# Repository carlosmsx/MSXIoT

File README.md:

# MSX IoT

## Internet de las cosas para MSX
Si estás en este sitio probablemente ya sabes lo que es un MSX.
Pero, has oído hablar de Internet de las cosas (Internet of Things)?
Te presento MSX IoT.

Es un cartucho para MSX que permite IoT y algunos extras muy interesantes:

* Conectarse a redes WiFi
* Conectarse a dispositivos BT
* Conectarse a dispositivos seriales (TTL)
* Audio
* Disco en la nube
* Unidades de red

Una vez conectado a una red WiFi, las posibilidades son muchas. Por ejemplo, es posible comandar dispositivos a través de internet, o bien saber el estado de los mismos.

A nivel de hardware, MSX IoT consta de una ROM, un decodificador de direcciones y un módulo ESP32.

Cada vez que el Z80 accede para lectura o escritura a un puerto designado en el decodificador, se genera una señal WAIT hacia el Z80 y paralelamente se lanza una interrupción en el ESP32. Esto permite que en el microcontrolador se compruebe si la interrupción se debe a una operación de entrada o salida. Con esto el ESP32 puede leer bytes enviados por el Z80, o bien enviarlos a solicitud del mismo. Es decir, el microcontrolador trabaja en modo esclavo. De esta manera es posible establecer intercambio de datos controlados desde el Z80. 

## Otras posibles habilidades del cartucho

### Cloud disk
Para esto es necesario implementar una unidad de disco que permita acceder a un repositorio en la nube. Sería ideal si se pudiese conectar a por ejemplo google drive. 
Mapear una unidad de red a una carpeta compartida de windows o linux.
### Audio
El ESP32 tiene la posibilidad de generar audio a través de dos salidas que poseen un DAC. Sabiendo esto, el cartucho tiene previsto evolucionar sobre este punto de manera de conectar estas salidas a la entrada de audio de MSX. En teoría sería posible generar sonidos tan complejos como la programación del ESP32 lo permita.
### RS232 TTL
Se ha dejado disponible una UART en el cartucho de manera que el cartucho sirva como una interfaz serie. 
Sería necesario implementar las extensiones BASIC correspondientes
- CALL COMBREAK
- CALL COMDTR
- CALL COM GOSUB
- CALL COMHELP
- CALL COMINI
- CALL COMOFF
- CALL COMON
- CALL COMSTAT
- CALL COMSTOP
- CALL COMTERM

© Carlos Escobar 2019

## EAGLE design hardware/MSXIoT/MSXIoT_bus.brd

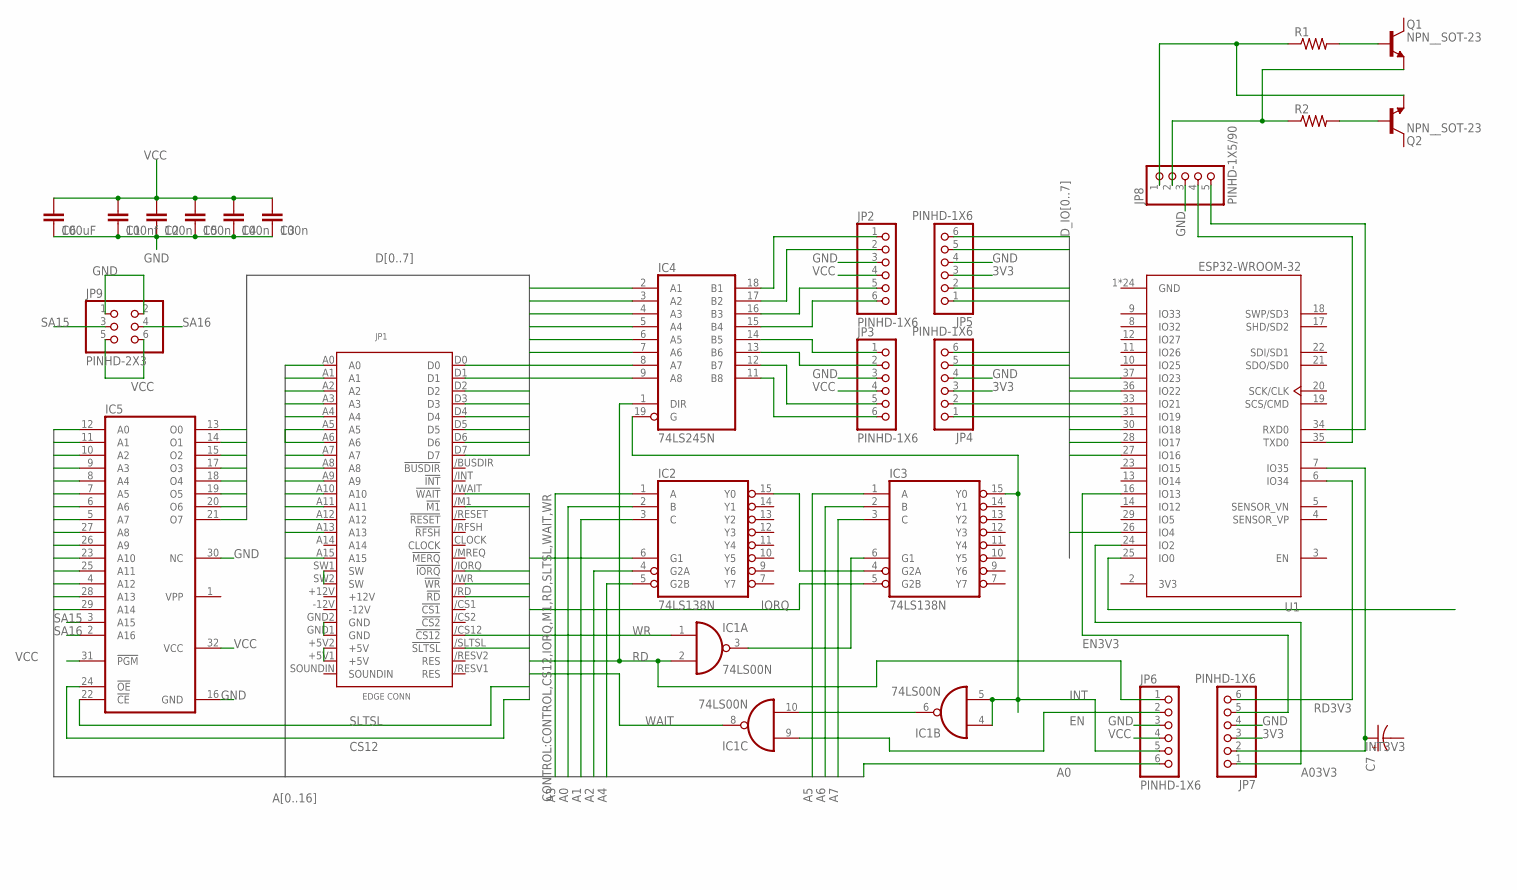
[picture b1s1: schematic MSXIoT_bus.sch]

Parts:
C1: 100nf; C2.5-2
C2, C3, C4, C5: 100n; C2.5-3
C6: 100uF; C2.5-6
C7: CPOL-US153CLV-0505; 153CLV-0505
IC1: 74LS00N; DIL14
IC2, IC3: 74LS138N; DIL16
IC4: 74LS245N; DIL20
IC5: 27C1001A; DIL32
JP1: MSXCART
JP2, JP3, JP4, JP5, JP6, JP7: PINHD-1X6; 1X06
JP8: PINHD-1X5/90; 1X05/90
JP9: PINHD-2X3; 2X03
Q1, Q2: NPN__SOT-23; SOT95P237X112-3N
R1, R2: R-US_0204/5; 0204/5
U1: ESP32-WROOM-32; MODULE_ESP32-WROOM-32

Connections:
3V3: JP4.3, JP5.3, JP7.3, U1.2 (3V3)
A0: IC2.2 (B), IC5.12 (A0), JP1.A0, JP6.6
A1: IC2.3 (C), IC5.11 (A1), JP1.A1
A2: IC2.4 (G2A), IC5.10 (A2), JP1.A2
A3: IC2.1 (A), IC5.9 (A3), JP1.A3
A03V3: JP7.1, U1.24 (IO2)
A4: IC2.5 (G2B), IC5.8 (A4), JP1.A4
A5: IC3.1 (A), IC5.7 (A5), JP1.A5
A6: IC3.2 (B), IC5.6 (A6), JP1.A6
A7: IC3.3 (C), IC5.5 (A7), JP1.A7
A8: IC5.27 (A8), JP1.A8
A9: IC5.26 (A9), JP1.A9
A10: IC5.23 (A10), JP1.A10
A11: IC5.25 (A11), JP1.A11
A12: IC5.4 (A12), JP1.A12
A13: IC5.28 (A13), JP1.A13
A14: IC5.29 (A14), JP1.A15
CS12: IC5.24 (!OE), JP1./CS12 (!CS12)
D0: IC4.2 (A1), IC5.13 (O0), JP1.D0
D1: IC4.3 (A2), IC5.14 (O1), JP1.D1
D2: IC4.4 (A3), IC5.15 (O2), JP1.D2
D3: IC4.5 (A4), IC5.17 (O3), JP1.D3
D4: IC4.6 (A5), IC5.18 (O4), JP1.D4
D5: IC4.7 (A6), IC5.19 (O5), JP1.D5
D6: IC4.8 (A7), IC5.20 (O6), JP1.D6
D7: IC4.9 (A8), IC5.21 (O7), JP1.D7
D_IO0: JP5.6, U1.37 (IO23)
D_IO1: JP5.5, U1.36 (IO22)
D_IO2: JP5.2, U1.33 (IO21)
D_IO3: JP5.1, U1.31 (IO19)
D_IO4: JP4.6, U1.30 (IO18)
D_IO5: JP4.5, U1.28 (IO17)
D_IO6: JP4.2, U1.27 (IO16)
D_IO7: JP4.1, U1.26 (IO4)
EN: IC1.9 (I0), JP6.2
EN3V3: JP7.5, U1.16 (IO13)
GND: C1.2, C2.2, C3.2, C4.2, C5.2, C6.2, IC1.7 (GND), IC2.8 (GND), IC3.8 (GND), IC4.10 (GND), IC5.16 (GND), IC5.30 (NC), JP1.GND1 (GND), JP1.GND2 (GND), JP2.3, JP3.3, JP4.4, JP5.4, JP6.3, JP7.4, JP8.3, JP9.1, JP9.2, U1.1 (GND), U1.15 (GND), U1.38 (GND), U1.39_1 (GND), U1.39_2 (GND), U1.39_3 (GND), U1.39_4 (GND), U1.39_5 (GND), U1.39_6 (GND), U1.39_7 (GND), U1.39_8 (GND), U1.39_9 (GND), U1.39_10 (GND), U1.39_11 (GND), U1.39_12 (GND), U1.39_13 (GND), U1.39_14 (GND), U1.39_15 (GND), U1.39_16 (GND), U1.39_17 (GND), U1.39_18 (GND), U1.39_19 (GND), U1.39_20 (GND), U1.39_21 (GND)
INT: IC1.4 (I0), IC1.5 (I1), IC3.15 (Y0), IC4.19 (G), JP6.5
INT3V3: C7.+, JP7.2, U1.7 (IO35)
IORQ: IC3.5 (G2B), JP1./IORQ (!IORQ)
M1: IC2.6 (G1), JP1./M1 (!M1)
unnamed: IC1.6 (O), IC1.10 (I1)
unnamed: IC4.18 (B1), JP2.1
unnamed: IC2.15 (Y0), IC3.4 (G2A)
unnamed: IC1.3 (O), IC3.6 (G1)
unnamed: IC4.17 (B2), JP2.2
unnamed: IC4.16 (B3), JP2.5
unnamed: IC4.15 (B4), JP2.6
unnamed: IC4.14 (B5), JP3.1
unnamed: IC4.13 (B6), JP3.2
unnamed: IC4.12 (B7), JP3.5
unnamed: IC4.11 (B8), JP3.6
unnamed: JP1.SW1 (SW), JP1.SW2 (SW)
unnamed: JP8.4, U1.35 (TXD0)
unnamed: JP8.5, U1.34 (RXD0)
unnamed: JP8.1, Q2.1 (E), R1.1
unnamed: Q1.2 (B), R1.2
unnamed: Q2.2 (B), R2.2
unnamed: JP8.2, Q1.1 (E), R2.1
RD: IC1.2 (I1), IC4.1 (DIR), JP1./RD (!RD), JP6.1
RD3V3: JP7.6, U1.6 (IO34)
SA15: IC5.3 (A15), JP9.3
SA16: IC5.2 (A16), JP9.4
SLTSL: IC5.22 (!CE), JP1./SLTSL (!SLTSL)
VCC: C1.1, C2.1, C3.1, C4.1, C5.1, C6.1, IC1.14 (VCC), IC2.16 (VCC), IC3.16 (VCC), IC4.20 (VCC), IC5.31 (!PGM), IC5.32 (VCC), JP1.+5V1 (+5V), JP1.+5V2 (+5V), JP2.4, JP3.4, JP6.4, JP9.5, JP9.6
WAIT: IC1.8 (O), JP1./WAIT (!WAIT)
WR: IC1.1 (I0), JP1./WR (!WR)

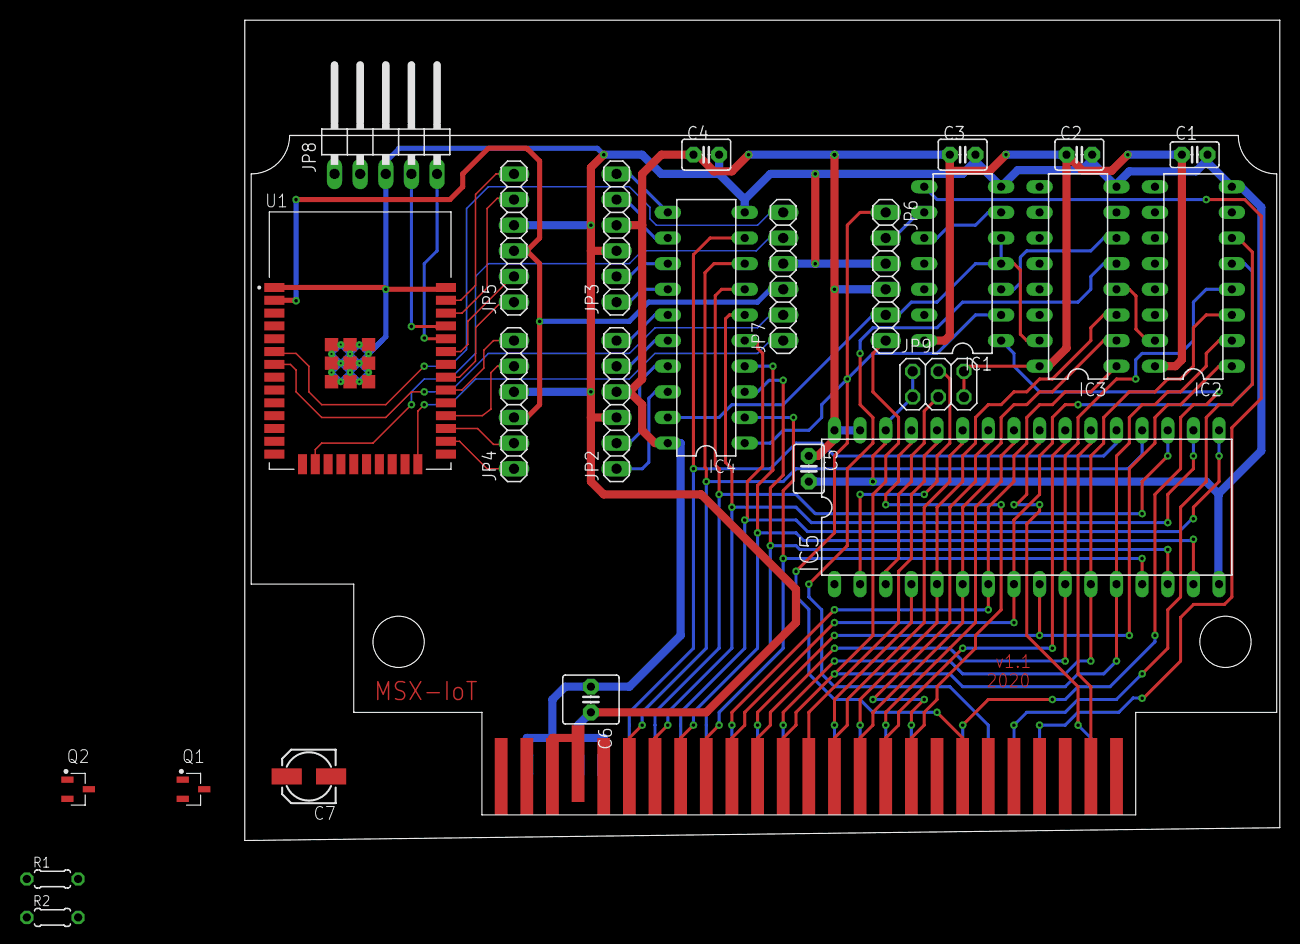
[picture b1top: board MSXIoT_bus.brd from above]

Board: 2 copper layers, 102.5 x 81.3 mm, 26 parts (0 on the bottom side), 67 nets.

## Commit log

2019-11-13 first upload
2019-11-22 primera subida
2019-11-22 cmake
2019-11-26 new extensions
2019-11-28 codigo de prueba
2019-11-28 reordenamiento
2019-11-28 reorder
2019-11-28 added firmware folder
2019-11-29 agregadas demoras a los puntos de I/O
2019-11-29 agregadas las nuevas funciones WCLIST, WPASS, WCONNECT, WDISCONNECT, WSTATUS, WLOAD y WBLOAD
2019-11-29 nuevas extensiones
2019-11-30 antes de implementar nuevos comandos
2019-12-03 casi todos los comandos WiFi implementados.
2019-12-04 primera version con que se conecta y toma IP
2019-12-06 Agregadas extensiones TCPSVR y TCPSEND. Muy alpha por ahora, pero funcionales
2020-01-15 agregado _FFILES
2020-02-26 reserva memoria en el workarea
2020-03-08 Agregada rutina en 8000H, y carga un archivo rom de prueba pero solo lo muestra por pantalla. Hay que implementar la rutina de swap a RAM y cargar directamente ahi.
2020-03-12 primera version que carga una ROM en memoria y la ejecuta correctamente.
2020-03-23 FFILES ahora lista tamaño. LOADROM carga ROMs de 16K y 32K. Todavía hay que probar bien la carga de 32K
2020-03-28 -Mejoras en el código en general. -Validación de errores para CLOUDROM. -agregada entrada GETLOG1 para evitar correr dos veces un comando (TCPSEND y CLOUDROM)
2020-06-16 info sobre cómo conectar la memoria flash. sirve para ROMS de 32K
2020-08-28 soporte para gdrive
2020-10-09 herramientas utiles basadas en arduino
2020-10-21 Prototipo de diskrom
2020-11-11 nueva version consoporte MSXDOS
2020-11-11 primera subida de firmware con soporte para MSXDOS
2020-11-22 primera subida:
2021-03-03 marzo2021
2021-08-10 new diskrom support
2021-08-12 DEFDPB error found and fixed
